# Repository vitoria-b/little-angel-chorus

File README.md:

# little-angel
Little Angel chorus pedal based on Rick Holt schematic.

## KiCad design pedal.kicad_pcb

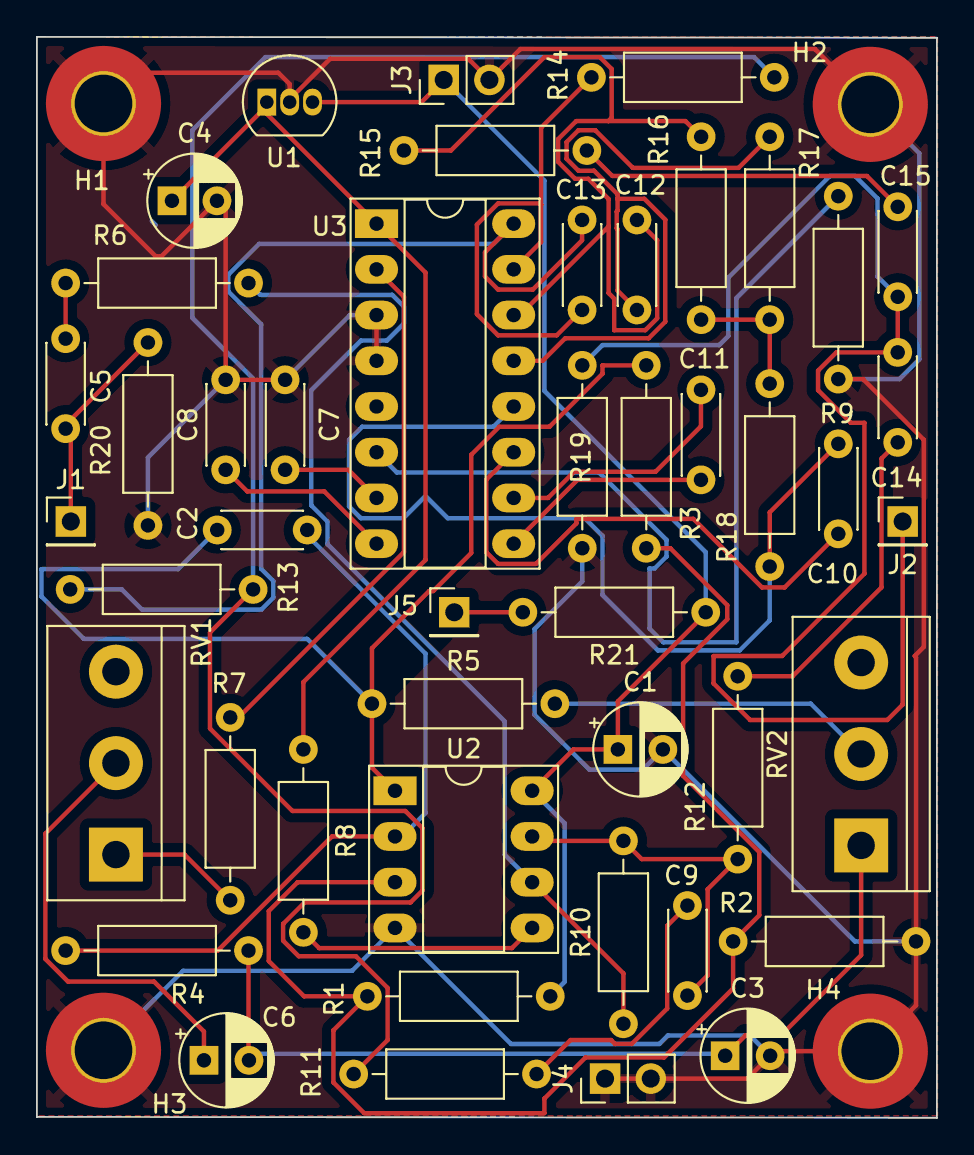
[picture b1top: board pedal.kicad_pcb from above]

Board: 2 copper layers, 50.0 x 60.0 mm, 50 parts (0 on the bottom side), 34 nets.

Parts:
C1: 100uF; CP_Radial_D5.0mm_P2.50mm
C2, C10, C11: 0.01uF; C_Disc_D4.3mm_W1.9mm_P5.00mm
C3, C6: 10uF; CP_Radial_D5.0mm_P2.50mm
C4: 47uF; CP_Radial_D5.0mm_P2.50mm
C5, C7, C8, C9, C14, C15: 0.1uF; C_Disc_D4.3mm_W1.9mm_P5.00mm
C12, C13: 0.001uF; C_Disc_D4.3mm_W1.9mm_P5.00mm
H1, H2, H3, H4: MountingHole_Pad; MountingHole_3.2mm_M3_Pad_TopBottom
J1, J2, J5: Conn_01x01_Female; PinHeader_1x01_P2.54mm_Vertical
J3, J4: Conn_01x02_Female; PinHeader_1x02_P2.54mm_Vertical
R1: 100k; R_Axial_DIN0207_L6.3mm_D2.5mm_P10.16mm_Horizontal
R2: 47k; R_Axial_DIN0207_L6.3mm_D2.5mm_P10.16mm_Horizontal
R3, R4: 220k; R_Axial_DIN0207_L6.3mm_D2.5mm_P10.16mm_Horizontal
R5: 4k7; R_Axial_DIN0207_L6.3mm_D2.5mm_P10.16mm_Horizontal
R6: 470k; R_Axial_DIN0207_L6.3mm_D2.5mm_P10.16mm_Horizontal
R7: 33k; R_Axial_DIN0207_L6.3mm_D2.5mm_P10.16mm_Horizontal
R8: 330k; R_Axial_DIN0207_L6.3mm_D2.5mm_P10.16mm_Horizontal
R9: 100R; R_Axial_DIN0207_L6.3mm_D2.5mm_P10.16mm_Horizontal
R10, R20: 1M; R_Axial_DIN0207_L6.3mm_D2.5mm_P10.16mm_Horizontal
R11, R12, R13, R14, R15, R16, R17, R18, R19: 10k; R_Axial_DIN0207_L6.3mm_D2.5mm_P10.16mm_Horizontal
R21: 330; R_Axial_DIN0207_L6.3mm_D2.5mm_P10.16mm_Horizontal
RV1: 470K Lin; TerminalBlock_bornier-3_P5.08mm
RV2: 100k Lin; TerminalBlock_bornier-3_P5.08mm
U1: L78L05_TO92; TO-92_Inline
U2: NE5532D8R2G; DIP-8_W7.62mm_Socket_LongPads
U3: PT2399; DIP-16_W7.62mm_Socket_LongPads

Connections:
/+ina: R1.2, R2.1, R3.1, U2.3 (+INA)
/+inb: R8.2, U2.5 (+INB)
/-ina: C2.2, R4.1, U2.2 (-INA)
/-inb: R6.1, R10.1, U2.6 (-INB)
/outa: C2.1, R3.2, R5.1, U2.1 (OUTA)
/outb: C9.2, R10.2, R12.1, U2.7 (OUTB)
Earth: C1.2, C3.2, C4.2, C7.2, C8.2, H1.1, H2.1, H3.1, H4.1, J3.2, J4.1, J4.2, R2.2, R9.1, R19.1, R20.1, U1.2 (GND), U2.4 (V-), U3.3 (AGND), U3.4 (DGND)
unnamed: C3.1, C6.2, R4.2, RV2.1
unnamed: C5.1, J1.1, R20.2
unnamed: C5.2, R6.2
unnamed: C6.1, RV1.2
unnamed: C7.1, U3.7 (CC1)
unnamed: C8.1, U3.8 (CC0)
unnamed: C9.1, R11.2
unnamed: C10.1, R18.1, U3.12 (OP2-OUT)
unnamed: C10.2, U3.11 (OP2-IN)
unnamed: C11.1, U3.10 (OP1-IN)
unnamed: C11.2, U3.9 (OP1-OUT)
unnamed: C12.1, R15.1, R16.1, U3.14 (LPF2-OUT)
unnamed: C12.2, R17.1, U3.13 (LPF2-IN)
unnamed: C13.1, R13.1, U3.16 (LPF1-IN)
unnamed: C13.2, R14.1, U3.15 (LPF1-OUT)
unnamed: C14.1, R12.2
unnamed: C14.2, C15.1, J2.1, R19.2
unnamed: C15.2, R15.2
unnamed: J5.1, R21.2
unnamed: R5.2, RV2.2
unnamed: R7.1, RV1.1
unnamed: R7.2, U3.2 (REF)
unnamed: C4.1, R8.1, U1.1 (VO), U3.1 (VCC)
unnamed: R9.2, U3.6 (VCO)
unnamed: R11.1, R13.2, R14.2
unnamed: R16.2, R17.2, R18.2
VCC: C1.1, J3.1, R1.1, R21.1, U1.3 (VI), U2.8 (V+)

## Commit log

2023-05-15 Adding project library
2023-05-22 doing the schematic
2023-05-22 doing the pcb layout
2023-05-23 updating project library
2023-05-23 adding ground plane and other fixes
2023-05-23 minor fixes and project settings
2023-05-23 adding gerbers and drill files
